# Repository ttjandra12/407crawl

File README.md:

# 407crawl: Inspection Robot for Pier and Beam Houses

Our design challenge is to design, prototype, and test a remote-controlled inspection robot that will allow a home owner or building inspector to inspect the underside condition of a pier and beam house. This GitHub page contains all the code and electronic schematics for the project.  

# Acknowledgements

This project is sponsored by John Treichler and Sally Wood.

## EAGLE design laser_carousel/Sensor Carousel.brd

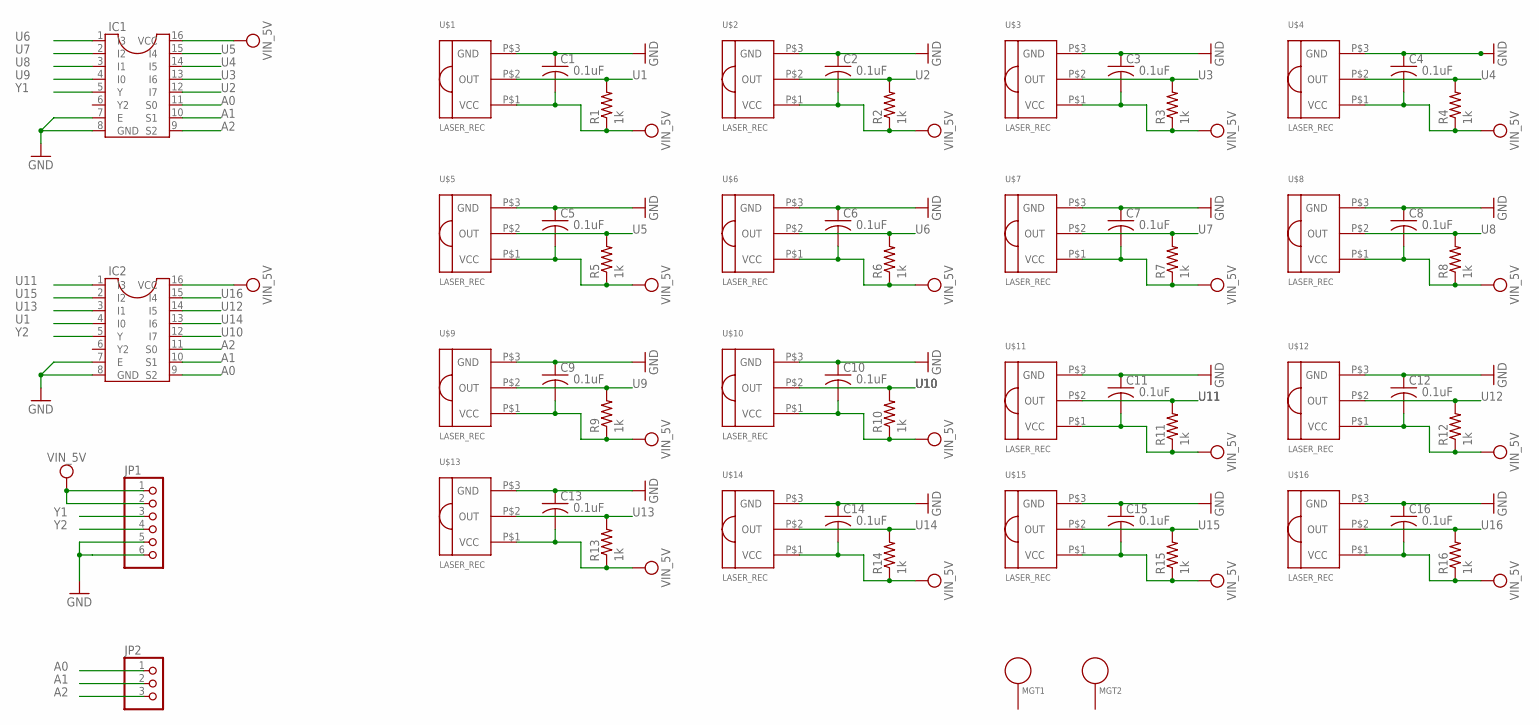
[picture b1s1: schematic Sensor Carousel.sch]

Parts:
C1, C2, C3, C4, C5, C6, C7, C8, C9, C10, C11, C12, C13, C14, C15, C16: 0.1uF; C025-024X044
IC1, IC2: CD74HCT151S; CD74HCT151
JP1: PINHD-1X6; 1X06
JP2: PINHD-1X3; 1X03
MGT1, MGT2: MOUNTING_HOLE
R1, R2, R3, R4, R5, R6, R7, R8, R9, R10, R11, R12, R13, R14, R15, R16: 1k; 0204V
U$1, U$2, U$3, U$4, U$5, U$6, U$7, U$8, U$9, U$10, U$11, U$12, U$13, U$14, U$15, U$16: LASER_REC; LSR_RC

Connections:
A0: IC1.11 (S0), IC2.9 (S2), JP2.1
A1: IC1.10 (S1), IC2.10 (S1), JP2.2
A2: IC1.9 (S2), IC2.11 (S0), JP2.3
GND: C1.1, C2.1, C3.1, C4.1, C5.1, C6.1, C7.1, C8.1, C9.1, C10.1, C11.1, C12.1, C13.1, C14.1, C15.1, C16.1, IC1.7 (E), IC1.8 (GND), IC2.7 (E), IC2.8 (GND), JP1.5, JP1.6, U$1.P$3 (GND), U$2.P$3 (GND), U$3.P$3 (GND), U$4.P$3 (GND), U$5.P$3 (GND), U$6.P$3 (GND), U$7.P$3 (GND), U$8.P$3 (GND), U$9.P$3 (GND), U$10.P$3 (GND), U$11.P$3 (GND), U$12.P$3 (GND), U$13.P$3 (GND), U$14.P$3 (GND), U$15.P$3 (GND), U$16.P$3 (GND)
U1: IC2.4 (I0), R1.2, U$1.P$2 (OUT)
U2: IC1.12 (I7), R2.2, U$2.P$2 (OUT)
U3: IC1.13 (I6), R3.2, U$3.P$2 (OUT)
U4: IC1.14 (I5), R4.2, U$4.P$2 (OUT)
U5: IC1.15 (I4), R5.2, U$5.P$2 (OUT)
U6: IC1.1 (I3), R6.2, U$6.P$2 (OUT)
U7: IC1.2 (I2), R7.2, U$7.P$2 (OUT)
U8: IC1.3 (I1), R8.2, U$8.P$2 (OUT)
U9: IC1.4 (I0), R9.2, U$9.P$2 (OUT)
U10: IC2.12 (I7), R10.2, U$10.P$2 (OUT)
U11: IC2.1 (I3), R11.2, U$11.P$2 (OUT)
U12: IC2.14 (I5), R12.2, U$12.P$2 (OUT)
U13: IC2.3 (I1), R13.2, U$13.P$2 (OUT)
U14: IC2.13 (I6), R14.2, U$14.P$2 (OUT)
U15: IC2.2 (I2), R15.2, U$15.P$2 (OUT)
U16: IC2.15 (I4), R16.2, U$16.P$2 (OUT)
VIN_5V: C1.2, C2.2, C3.2, C4.2, C5.2, C6.2, C7.2, C8.2, C9.2, C10.2, C11.2, C12.2, C13.2, C14.2, C15.2, C16.2, IC1.16 (VCC), IC2.16 (VCC), JP1.1, JP1.2, R1.1, R2.1, R3.1, R4.1, R5.1, R6.1, R7.1, R8.1, R9.1, R10.1, R11.1, R12.1, R13.1, R14.1, R15.1, R16.1, U$1.P$1 (VCC), U$2.P$1 (VCC), U$3.P$1 (VCC), U$4.P$1 (VCC), U$5.P$1 (VCC), U$6.P$1 (VCC), U$7.P$1 (VCC), U$8.P$1 (VCC), U$9.P$1 (VCC), U$10.P$1 (VCC), U$11.P$1 (VCC), U$12.P$1 (VCC), U$13.P$1 (VCC), U$14.P$1 (VCC), U$15.P$1 (VCC), U$16.P$1 (VCC)
Y1: IC1.5 (Y), JP1.3
Y2: IC2.5 (Y), JP1.4

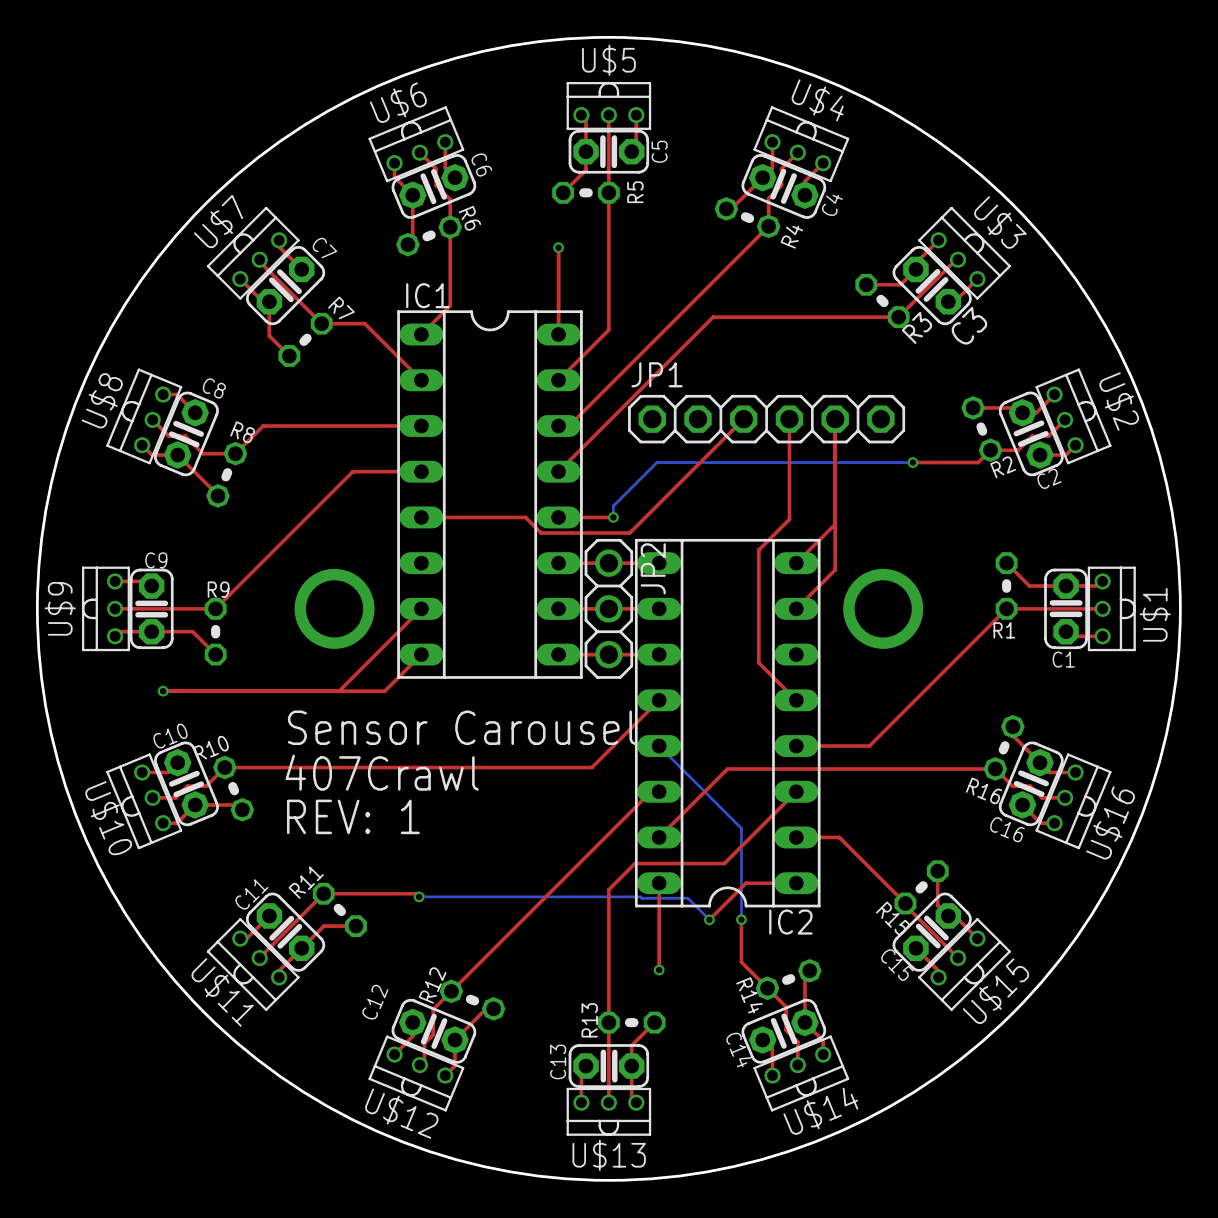
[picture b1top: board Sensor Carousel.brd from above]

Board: 2 copper layers, 63.5 x 63.5 mm, 54 parts (0 on the bottom side), 23 nets.

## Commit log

2019-01-19 add SD card reader ino file
2019-01-20 updated code with comments
2019-01-20 added readme
2019-01-20 added code for ToF sensor
2019-01-21 updated DAQ code
2019-01-28 Added the code for the RC Controller: servo, motor, and channel read outs
2019-01-30 Added the Arduino folder
2019-01-30 Re organized some of the files and did some updates.
2019-01-31 added excel draft
2019-01-31 Updated the motor driver code.
2019-02-03 Added the servo control to the motor controller code and renamed file.
2019-02-03 created SW folder
2019-02-04 MOAR UPLOADS
    Uploaded old spirit level arduino code and laser test program
2019-02-04 First pass of everything
2019-02-05 Initial commit
    These are the first prototype components for the scissor jack lift
2019-02-05 initial commit
    Scissor jack assembly upload (it's a piece of shit)
2019-02-05 McMaster Carr Parts
    $$$$
2019-02-05 Initial commit of PCB
    Its a PCB yo!
2019-02-05 Rename the servo control file
2019-02-06 Added the Excel file with a macro and a test CSV file.
2019-02-06 Updated formating in the Excel (macros) file
2019-02-06 Carousel PCB Updates
2019-02-09 More Board Committs
2019-02-09 Tribrach Committs
2019-02-11 Tribrach edits for green laser
2019-02-11 Added the camera mount file
2019-02-12 scissor jack v2 SW files
2019-02-12 Updated SW Assembly
2019-02-12 Revised v2 Assembly
2019-02-12 Updated the controller code
2019-02-13 Updated SW Files
2019-02-13 Updated scissor_jack SW Assembly
2019-02-13 Updated v2 Assembly
2019-02-14 New tribrach supports
2019-02-14 New Camera Mount
2019-02-14 Updated SW Assm
2019-02-17 Updated SW File
2019-02-17 Leveling Platform Code Initial Commit
    Using BN005 - Work in Progress
2019-02-18 Additional SW Updates and Torque Calcs
2019-02-19 More SW Updates
2019-02-19 Updated SW
2019-02-20 Added 360 Servo Code
2019-02-20 Updated Code
2019-02-20 More controller code
2019-02-22 Added a new test code for the 360 degree servo
2019-02-22 Updated green laser holder
    tolerance adjustment
2019-02-23 Updated Servo Code
2019-02-25 Added SW File
2019-02-25 Added the ToF sensor to the RC controller and included a library for the sensor
2019-02-26 Updated Scissor Jack Code
2019-02-28 Sensor Carousel Updates
2019-02-28 Carousel Holder Solidworks
2019-02-28 Added RC controller code for the continuous servo.
2019-02-28 Updated Interrupt Code
2019-03-01 Leveling Platform V3
    The Correct Leveling platform. Just realized I wasn't working from the github file.
2019-03-01 Carousel Stand Updates
2019-03-01 Updated the continuous servo code
2019-03-02 Added Height Calculations Ref
2019-03-03 Added the SD card reader into the controller code and included an extra Library
2019-03-03 Added .h Files to Final Code
2019-03-03 Updated controller code
2019-03-03 Add Laser Carousel Code
2019-03-03 Updated Scissor Jack CAD
2019-03-04 Deleted duplicated file
2019-03-04 Added the sensor carousel to the main code
2019-03-04 Update Level_Platform_Code.ino
    Hopefully Final Update. Can be put into the main code. pin numbers for motors need to be changed
2019-03-04 Updated the general code
2019-03-05 Update Level_Platform_Code.ino
    Ready to be put on the FINAL code and tried out
2019-03-05 Updated RC controller code
2019-03-05 Deleted a duplicated folder
2019-03-06 Updated codes
2019-03-06 Update Level_Platform_Code.ino
    To show that the motors work and delays to improve the jittering. will focus on more past mid-term review
2019-03-06 The CAD files for the level holder
    The CAD files from my computer
2019-03-06 Added Macro V2
2019-03-07 Updated the final controller code
2019-03-19 Scissor Jack V3
2019-03-24 Updated main controller code
2019-03-28 Added AL Scissor Arm CAD
2019-03-31 Chassis start
2019-03-31 Added Python Data Proc Code
2019-04-01 Updated the sensor carousel code with the correct pin locations
2019-04-01 Added Engineering Drawings
2019-04-02 Continue
2019-04-02 Fixing Jittering Issue
    - Yservo jittering issue is solved
    - Xservo jittering issue needs to be solved
2019-04-02 Level Platfrom Drawings
    Not finished yet
2019-04-02 Drawings for Level Platform
    Almost Finished
2019-04-03 updated cad
2019-04-03 Added the schematic of the sensor carousel
2019-04-03 Assembly Drawings Completed
2019-04-03 Code Update
2019-04-03 New Scissor Jack Top
    Added cuttout for wire pass through
2019-04-03 Added ToF Platform
2019-04-03 Created new code to include to ToF sensors
2019-04-04 Update Level_Platform_Code.ino
    New update to make improvements
2019-04-04 Update Level_Platform_Code.ino
    Change to make the system move faster
2019-04-04 Successful entry widget code
2019-04-04 New carousel stand
2019-04-04 Update Level_Platform_Code.ino
    FINAL
2019-04-04 Updated main code
2019-04-04 Update Device_Code.ino
    MPU Working, but the loop for level needs to run more than once. using a while loop to fix
2019-04-05 work
2019-04-05 Updated the code
2019-04-05 solid work chassis
    idk what changes
2019-04-05 update to level code and device code
    Updates. One servo is not working
2019-04-05 M2 holes and scooted pin hole in
2019-04-07 updates (including new arduino platform)
2019-04-07 Updated Scissor Jack Assembly
2019-04-08 assembly updates
2019-04-08 updates?
2019-04-08 Updated the code to make the sensor carousel work and added the dummy control of the scissor jack (which is untested)
2019-04-09 Total Assembly
    Coloring done
2019-04-16 leveling platform v3
2019-04-17 platform new servos
2019-04-20 Modified timing budget to increase accuracy of ToF sensors
2019-04-21 1st printed version platform
